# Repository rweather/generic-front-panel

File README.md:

Generic Front Panel
===================

This repository contains schematics and other information for a generic
front panel for 8-bit homebrew computers.

Here it is connected to my version of
[Ben Eater's 6502 Breadboard Computer](https://eater.net/6502),
running the "hello.s" example from the "src/6502" directory.
It is shown here after I typed ABCDEF on the keypad:

Here is a close-up of the front panel with a 3D-printed plate over the top:

The "print" directory contains an OpenSCAD file for the 3D-printable plate.
My brother, who is into 3D-printing, has a textured print bed for his printer.
He printed the plate upside down and the texturing gave the plate a nice finish.

## Features

The generic front panel has the following features:

* 6-digit seven segment display.
* 16-digit hexadecimal keypad.
* 3 extra keys for "CMD1", "CMD2", and "CMD3" which can be assigned
  any commands you like by your software.
* 1 extra key for a system reset button.
* 20-pin connector to the rest of your homebrew system.
* Power LED for the 5V power rail.

Note that this front panel requires software support.  It doesn't directly
operate the address bus, data bus, clock, and other control lines like
front panels of old.

What this front panel does do is make it easy to write a memory monitor in
software that can examine memory, modify memory, single-step, and so on.
The 6 displays can display a 16-bit address and an 8-bit byte.  Or anything
else you like, even words.

The seven segment displays, keypad buttons, and power LED are mounted
on the front side of the PCB.  All other components are mounted on the
back side.  The inline current limiting resistors are specified as 8-way
resistor arrays.  However, you could fit 8 regular resistors side by side
instead.

The front panel draws about 250mA from the 5V rail when all 48 segments
in the 7-segment displays and the power LED are lit.  About 5mA per segment.

I have provided drivers and examples for various CPU's under the
"src" directory.  Patches welcome for other CPU's and homebrew boards.

## Schematic and gerber files

* [PDF of the schematic](schematics/Generic_Front_Panel/PDF/Generic_Front_Panel.pdf)
* [Gerber files for manufacture](schematics/Generic_Front_Panel/Gerbers)

The dimensions of the PCB are 195mm x 90mm.  Five 3mm mounting holes are
provided for mounting behind a face plate: four corners and one in the
centre for added strength.

## Parts list

* 1 x Generic Front Panel FP-01 PCB
* 1 x 74HC138 3-line to 8-line decoder (74LS138 or 74HCT138 can be substituted)
* 1 x 74HC244 octal buffer / line driver (74LS244 or 74HCT244 can be substituted)
* 6 x 74HC259 addressable latch (74LS259 or 74HCT239 can be substituted)
* 6 x 100nF ceramic or monolithic capacitor
* 5 x 100pF ceramic capacitor
* 1 x 100uF electrolytic capacitor, rated for 6.3V or better
* 6 x 470 ohm DIP-16 resistor array
* 5 x 4.7K ohm resistor
* 1 x 220 ohm resistor (series resistor for 5mm power LED, adjust value for the LED's current rating)
* 1 x 5mm LED for the power LED (color is up to you)
* 6 x MAN71A 7-segment LED display (TIL-312 or Broadcom 5082-7611 can be substituted)
* 5 x 1N4148 diode
* 20 x 12mm push button plus keycaps
* 1 x 20-pin 2.54mm pitch terminal header or socket for the J1 connector

I recommend using DIP-14 sockets for the 7-segment LED displays to
raise the height of the displays up to roughly level with the top of the
push buttons plus keycaps.  Sockets for the other IC's are up to you;
I didn't bother.

Labels can be applied to the keycaps using a label maker and clear labels.

This is what the front and back of the PCB looks like once assembled
(I had only done a very basic board clean at this point so it is still a
little smudgy):

## 20-pin connector

The connector on the bottom of the PCB has the following pins:

<table border="1">
<tr><td><b>Pin</b></td><td><b>Description</b></td></tr>
<tr><td>1</td><td>+5V</td></tr>
<tr><td>2</td><td>D0</td></tr>
<tr><td>3</td><td>D1</td></tr>
<tr><td>4</td><td>D2</td></tr>
<tr><td>5</td><td>D3</td></tr>
<tr><td>6</td><td>D4</td></tr>
<tr><td>7</td><td>D5</td></tr>
<tr><td>8</td><td>D6</td></tr>
<tr><td>9</td><td>D7</td></tr>
<tr><td>10</td><td>A0</td></tr>
<tr><td>11</td><td>A1</td></tr>
<tr><td>12</td><td>A2</td></tr>
<tr><td>13</td><td>A3</td></tr>
<tr><td>14</td><td>A4</td></tr>
<tr><td>15</td><td>A5</td></tr>
<tr><td>16</td><td>Select Display (active low)</td></tr>
<tr><td>17</td><td>Select Keypad (active low)</td></tr>
<tr><td>18</td><td>Reset (active low)</td></tr>
<tr><td>19</td><td>GND</td></tr>
<tr><td>20</td><td>GND</td></tr>
</table>

## Chip selects

To interface to your homebrew computer, you will need to provide address
decoding for the two "chip select" lines "Select Display" and "Select Keypad".

You can put the front panel anywhere in memory or I/O space that is
aligned on a 64-byte boundary.  Only the bottom 6 address bits are
provided to the front panel.  You need to decode the upper 10 bits
(of a 16-bit address) yourself by some means.

"Select Display" should be low when the top-most bits of the address
match the location in memory where you want to put the display,
and when the bus is in a write cycle.  The display occupies 64 bytes
of memory space.

"Select Keypad" should be low when the top-most bits of the address
match the location in memory where you want to put the keypad,
and when the bus is in a read cycle.  The keypad occupies 32 bytes
of memory space.  It can overlap with the display in memory if that
is easier.

## Writing to the display

Each segment of the display has its own memory address.  Each digit
occupies 8 bytes of memory space, for the segments A, B, C, D, E, F, G,
and decimal point.  The displays are at offsets 0, 8, 16, 24, 32,
and 40 in the memory space.

Write a byte with the low bit set to 0 to a segment's address to turn
the segment on, or write a byte with the low bit set to 1 to turn the
segment off.  The segment will stay lit until modified or the power is
turned off.  The display is not multiplexed so there is no need to
constantly refresh.

Writing any byte value to offset 56 will turn all segments on.
This can be useful for testing.  Normally you will want to turn
everything off at startup time.

The "one byte per segment" design was borrowed from the Heathkit ET-3400.
74HC259 addressable latches are used to individually address each segment,
and to remember the state of the segment between writes.

## Reading from the keypad

The keypad consists of 5 rows of 4 keys.  The rows are associated with
address bits A0 to A4.  Scan through the keypad one row at a time,
setting one address bit to 0 and the rest to 1.  When you read from that
address, the bits that are set to zero indicate which keys are pressed
on that row.

<table border="1">
<tr><td><b>Address</b></td><td><b>Bit</b></td><td><b>Key</b></td></tr>
<tr><td>$XX1E (A0)</td><td>0</td><td>0</td></tr>
<tr><td>$XX1E (A0)</td><td>1</td><td>1</td></tr>
<tr><td>$XX1E (A0)</td><td>2</td><td>2</td></tr>
<tr><td>$XX1E (A0)</td><td>3</td><td>3</td></tr>
<tr><td>$XX1D (A1)</td><td>0</td><td>4</td></tr>
<tr><td>$XX1D (A1)</td><td>1</td><td>5</td></tr>
<tr><td>$XX1D (A1)</td><td>2</td><td>6</td></tr>
<tr><td>$XX1D (A1)</td><td>3</td><td>7</td></tr>
<tr><td>$XX1B (A2)</td><td>0</td><td>8</td></tr>
<tr><td>$XX1B (A2)</td><td>1</td><td>9</td></tr>
<tr><td>$XX1B (A2)</td><td>2</td><td>A</td></tr>
<tr><td>$XX1B (A2)</td><td>3</td><td>B</td></tr>
<tr><td>$XX17 (A3)</td><td>0</td><td>C</td></tr>
<tr><td>$XX17 (A3)</td><td>1</td><td>D</td></tr>
<tr><td>$XX17 (A3)</td><td>2</td><td>E</td></tr>
<tr><td>$XX17 (A3)</td><td>3</td><td>F</td></tr>
<tr><td>$XX0F (A4)</td><td>0</td><td>CMD1</td></tr>
<tr><td>$XX0F (A4)</td><td>1</td><td>CMD2</td></tr>
<tr><td>$XX0F (A4)</td><td>2</td><td>CMD3</td></tr>
<tr><td>$XX0F (A4)</td><td>3</td><td>(not used)</td></tr>
</table>

The "Reset" key is special.  It will pull pin 18 on the connector
down to GND when pressed.  It is assumed that a pull-up resistor and
debouncing capacitor are present on your main computer board.
If you want to use "Reset" for something else (such as a "CMD4" key),
you can connect pin 18 to an I/O pin on your main computer board.

The "rows as addresses" design was borrowed from the VZ200 / Laser 200.
Only a single 74HC244 bus transceiver is required to read the keypad.
Everything else is pushbuttons, diodes, resistors, and capacitors.

There are jumpers on the back of the board that can be cut to wire
up additional keys if you need more than 20.  The extra keys will
be available as bits 4 through 7.  The bits are pulled high if the
jumpers are uncut.

## License

MIT License.

## Contact

For more information on this project, to report bugs, or to suggest
improvements, please contact the author Rhys Weatherley via
[email](mailto:rhys.weatherley@gmail.com).

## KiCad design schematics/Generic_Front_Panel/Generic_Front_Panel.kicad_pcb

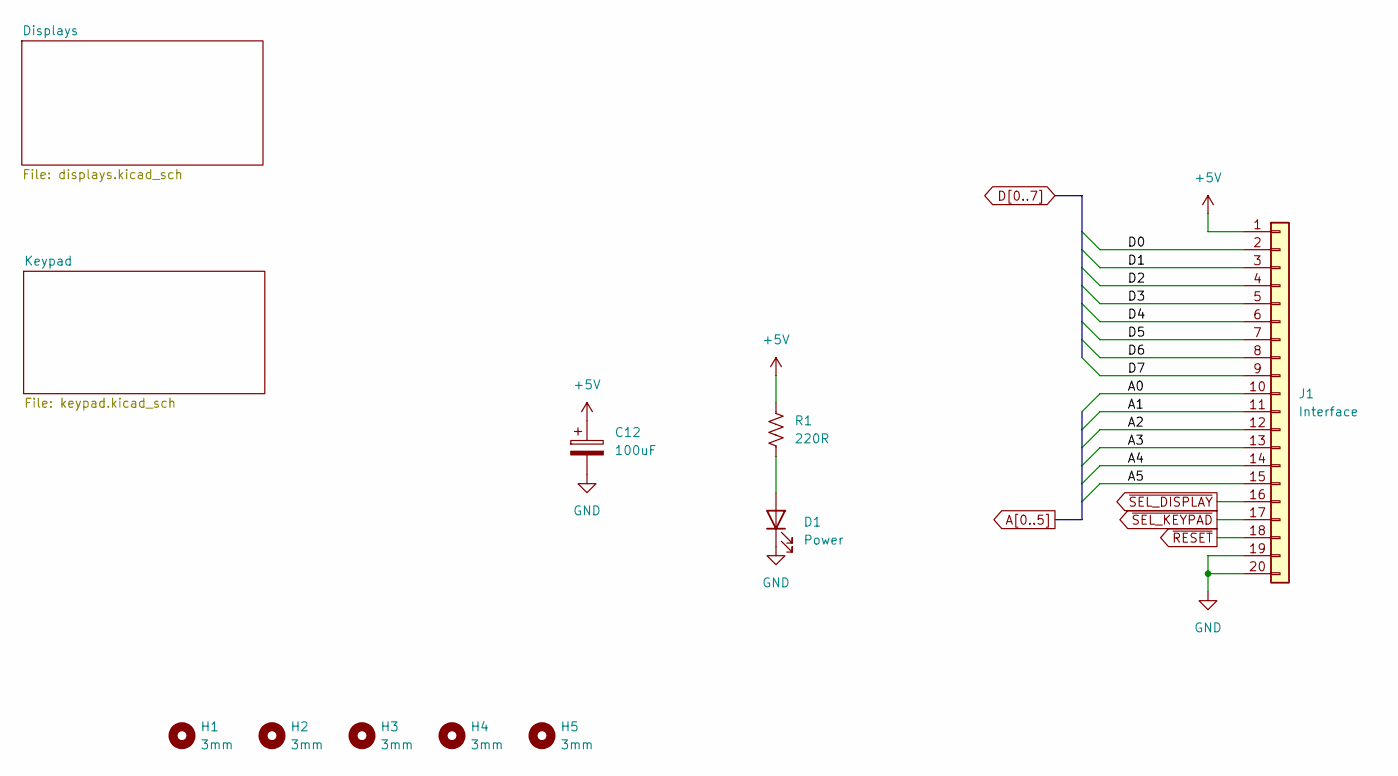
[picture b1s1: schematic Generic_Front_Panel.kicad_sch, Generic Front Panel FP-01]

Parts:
C12: 100uF; CP_Radial_D6.3mm_P2.50mm
D1: Power; LED_D5.0mm
H1, H2, H3, H4, H5: 3mm; MountingHole_3mm
J1: Interface; PinSocket_1x20_P2.54mm_Vertical
R1: 220R; R_Axial_DIN0207_L6.3mm_D2.5mm_P10.16mm_Horizontal

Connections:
+5V: C12.1, J1.1, R1.1; also elsewhere on the board
A0: J1.10; also elsewhere on the board
A1: J1.11; also elsewhere on the board
A2: J1.12; also elsewhere on the board
A3: J1.13; also elsewhere on the board
A4: J1.14; also elsewhere on the board
A5: J1.15; also elsewhere on the board
D0: J1.2; also elsewhere on the board
D1: J1.3; also elsewhere on the board
D2: J1.4; also elsewhere on the board
D3: J1.5; also elsewhere on the board
D4: J1.6; also elsewhere on the board
D5: J1.7; also elsewhere on the board
D6: J1.8; also elsewhere on the board
D7: J1.9; also elsewhere on the board
GND: C12.2, D1.1 (K), J1.19, J1.20; also elsewhere on the board
unnamed: D1.2 (A), R1.2
~RESET: J1.18; also elsewhere on the board
~SEL_DISPLAY: J1.16; also elsewhere on the board
~SEL_KEYPAD: J1.17; also elsewhere on the board

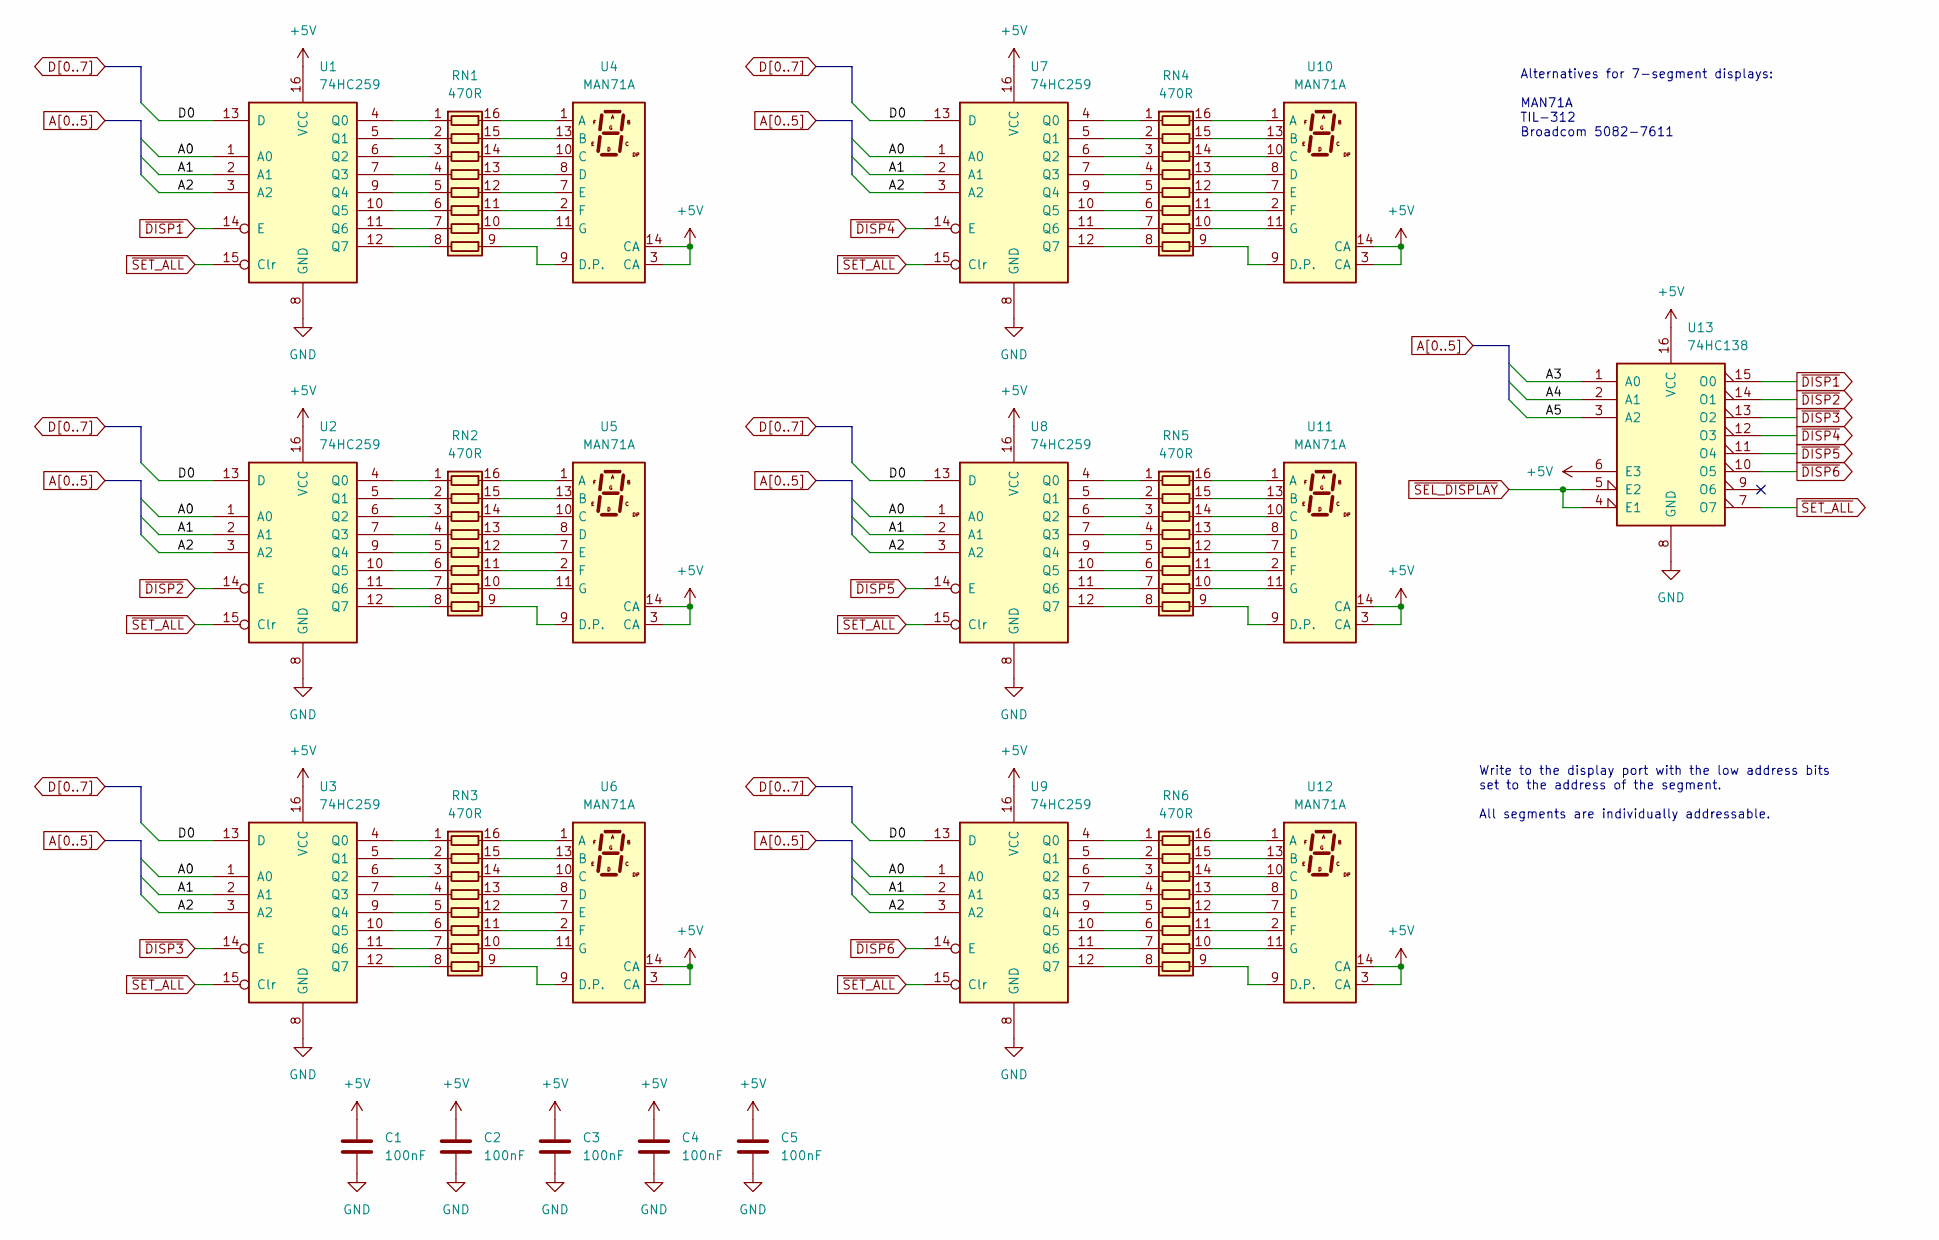
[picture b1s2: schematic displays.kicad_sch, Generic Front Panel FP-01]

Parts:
C1, C2, C3, C4, C5: 100nF; C_Disc_D6.0mm_W2.5mm_P5.00mm
RN1, RN2, RN3, RN4, RN5, RN6: 470R; DIP-16_W7.62mm
U1, U2, U3, U7, U8, U9: 74HC259; DIP-16_W7.62mm
U4, U5, U6, U10, U11, U12: MAN71A
U13: 74HC138; DIP-16_W7.62mm

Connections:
+5V: C1.1, C2.1, C3.1, C4.1, C5.1, U1.16 (VCC), U2.16 (VCC), U3.16 (VCC), U4.3 (CA), U4.14 (CA), U5.3 (CA), U5.14 (CA), U6.3 (CA), U6.14 (CA), U7.16 (VCC), U8.16 (VCC), U9.16 (VCC), U10.3 (CA), U10.14 (CA), U11.3 (CA), U11.14 (CA), U12.3 (CA), U12.14 (CA), U13.6 (E3), U13.16 (VCC); also elsewhere on the board
A0: U1.1 (A0), U2.1 (A0), U3.1 (A0), U7.1 (A0), U8.1 (A0), U9.1 (A0); also elsewhere on the board
A1: U1.2 (A1), U2.2 (A1), U3.2 (A1), U7.2 (A1), U8.2 (A1), U9.2 (A1); also elsewhere on the board
A2: U1.3 (A2), U2.3 (A2), U3.3 (A2), U7.3 (A2), U8.3 (A2), U9.3 (A2); also elsewhere on the board
A3: U13.1 (A0); also elsewhere on the board
A4: U13.2 (A1); also elsewhere on the board
A5: U13.3 (A2); also elsewhere on the board
D0: U1.13 (D), U2.13 (D), U3.13 (D), U7.13 (D), U8.13 (D), U9.13 (D); also elsewhere on the board
GND: C1.2, C2.2, C3.2, C4.2, C5.2, U1.8 (GND), U2.8 (GND), U3.8 (GND), U7.8 (GND), U8.8 (GND), U9.8 (GND), U13.8 (GND); also elsewhere on the board
unnamed: RN1.1 (R1.1), U1.4 (Q0)
unnamed: RN1.16 (R1.2), U4.1 (A)
unnamed: RN1.2 (R2.1), U1.5 (Q1)
unnamed: RN1.15 (R2.2), U4.13 (B)
unnamed: RN1.3 (R3.1), U1.6 (Q2)
unnamed: RN1.14 (R3.2), U4.10 (C)
unnamed: RN1.4 (R4.1), U1.7 (Q3)
unnamed: RN1.13 (R4.2), U4.8 (D)
unnamed: RN1.5 (R5.1), U1.9 (Q4)
unnamed: RN1.12 (R5.2), U4.7 (E)
unnamed: RN1.6 (R6.1), U1.10 (Q5)
unnamed: RN1.11 (R6.2), U4.2 (F)
unnamed: RN1.7 (R7.1), U1.11 (Q6)
unnamed: RN1.10 (R7.2), U4.11 (G)
unnamed: RN1.8 (R8.1), U1.12 (Q7)
unnamed: RN1.9 (R8.2), U4.9 (D.P.)
unnamed: RN2.1 (R1.1), U2.4 (Q0)
unnamed: RN2.16 (R1.2), U5.1 (A)
unnamed: RN2.2 (R2.1), U2.5 (Q1)
unnamed: RN2.15 (R2.2), U5.13 (B)
unnamed: RN2.3 (R3.1), U2.6 (Q2)
unnamed: RN2.14 (R3.2), U5.10 (C)
unnamed: RN2.4 (R4.1), U2.7 (Q3)
unnamed: RN2.13 (R4.2), U5.8 (D)
unnamed: RN2.5 (R5.1), U2.9 (Q4)
unnamed: RN2.12 (R5.2), U5.7 (E)
unnamed: RN2.6 (R6.1), U2.10 (Q5)
unnamed: RN2.11 (R6.2), U5.2 (F)
unnamed: RN2.7 (R7.1), U2.11 (Q6)
unnamed: RN2.10 (R7.2), U5.11 (G)
unnamed: RN2.8 (R8.1), U2.12 (Q7)
unnamed: RN2.9 (R8.2), U5.9 (D.P.)
unnamed: RN3.1 (R1.1), U3.4 (Q0)
unnamed: RN3.16 (R1.2), U6.1 (A)
unnamed: RN3.2 (R2.1), U3.5 (Q1)
unnamed: RN3.15 (R2.2), U6.13 (B)
unnamed: RN3.3 (R3.1), U3.6 (Q2)
unnamed: RN3.14 (R3.2), U6.10 (C)
unnamed: RN3.4 (R4.1), U3.7 (Q3)
unnamed: RN3.13 (R4.2), U6.8 (D)
unnamed: RN3.5 (R5.1), U3.9 (Q4)
unnamed: RN3.12 (R5.2), U6.7 (E)
unnamed: RN3.6 (R6.1), U3.10 (Q5)
unnamed: RN3.11 (R6.2), U6.2 (F)
unnamed: RN3.7 (R7.1), U3.11 (Q6)
unnamed: RN3.10 (R7.2), U6.11 (G)
unnamed: RN3.8 (R8.1), U3.12 (Q7)
unnamed: RN3.9 (R8.2), U6.9 (D.P.)
unnamed: RN4.1 (R1.1), U7.4 (Q0)
unnamed: RN4.16 (R1.2), U10.1 (A)
unnamed: RN4.2 (R2.1), U7.5 (Q1)
unnamed: RN4.15 (R2.2), U10.13 (B)
unnamed: RN4.3 (R3.1), U7.6 (Q2)
unnamed: RN4.14 (R3.2), U10.10 (C)
unnamed: RN4.4 (R4.1), U7.7 (Q3)
unnamed: RN4.13 (R4.2), U10.8 (D)
unnamed: RN4.5 (R5.1), U7.9 (Q4)
unnamed: RN4.12 (R5.2), U10.7 (E)
unnamed: RN4.6 (R6.1), U7.10 (Q5)
unnamed: RN4.11 (R6.2), U10.2 (F)
unnamed: RN4.7 (R7.1), U7.11 (Q6)
unnamed: RN4.10 (R7.2), U10.11 (G)
unnamed: RN4.8 (R8.1), U7.12 (Q7)
unnamed: RN4.9 (R8.2), U10.9 (D.P.)
unnamed: RN5.1 (R1.1), U8.4 (Q0)
unnamed: RN5.16 (R1.2), U11.1 (A)
unnamed: RN5.2 (R2.1), U8.5 (Q1)
unnamed: RN5.15 (R2.2), U11.13 (B)
unnamed: RN5.3 (R3.1), U8.6 (Q2)
unnamed: RN5.14 (R3.2), U11.10 (C)
unnamed: RN5.4 (R4.1), U8.7 (Q3)
unnamed: RN5.13 (R4.2), U11.8 (D)
unnamed: RN5.5 (R5.1), U8.9 (Q4)
unnamed: RN5.12 (R5.2), U11.7 (E)
unnamed: RN5.6 (R6.1), U8.10 (Q5)
unnamed: RN5.11 (R6.2), U11.2 (F)
unnamed: RN5.7 (R7.1), U8.11 (Q6)
unnamed: RN5.10 (R7.2), U11.11 (G)
unnamed: RN5.8 (R8.1), U8.12 (Q7)
unnamed: RN5.9 (R8.2), U11.9 (D.P.)
unnamed: RN6.1 (R1.1), U9.4 (Q0)
unnamed: RN6.16 (R1.2), U12.1 (A)
unnamed: RN6.2 (R2.1), U9.5 (Q1)
unnamed: RN6.15 (R2.2), U12.13 (B)
unnamed: RN6.3 (R3.1), U9.6 (Q2)
unnamed: RN6.14 (R3.2), U12.10 (C)
unnamed: RN6.4 (R4.1), U9.7 (Q3)
unnamed: RN6.13 (R4.2), U12.8 (D)
unnamed: RN6.5 (R5.1), U9.9 (Q4)
unnamed: RN6.12 (R5.2), U12.7 (E)
unnamed: RN6.6 (R6.1), U9.10 (Q5)
unnamed: RN6.11 (R6.2), U12.2 (F)
unnamed: RN6.7 (R7.1), U9.11 (Q6)
unnamed: RN6.10 (R7.2), U12.11 (G)
unnamed: RN6.8 (R8.1), U9.12 (Q7)
unnamed: RN6.9 (R8.2), U12.9 (D.P.)
~DISP1: U1.14 (E), U13.15 (O0)
~DISP2: U2.14 (E), U13.14 (O1)
~DISP3: U3.14 (E), U13.13 (O2)
~DISP4: U7.14 (E), U13.12 (O3)
~DISP5: U8.14 (E), U13.11 (O4)
~DISP6: U9.14 (E), U13.10 (O5)
~SEL_DISPLAY: U13.4 (E1), U13.5 (E2); also elsewhere on the board
~SET_ALL: U1.15 (Clr), U2.15 (Clr), U3.15 (Clr), U7.15 (Clr), U8.15 (Clr), U9.15 (Clr), U13.7 (O7)

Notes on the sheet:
Write to the display port with the low address bits set to the address of the segment. All segments are individually addressable.
Alternatives for 7-segment displays: MAN71A TIL-312 Broadcom 5082-7611

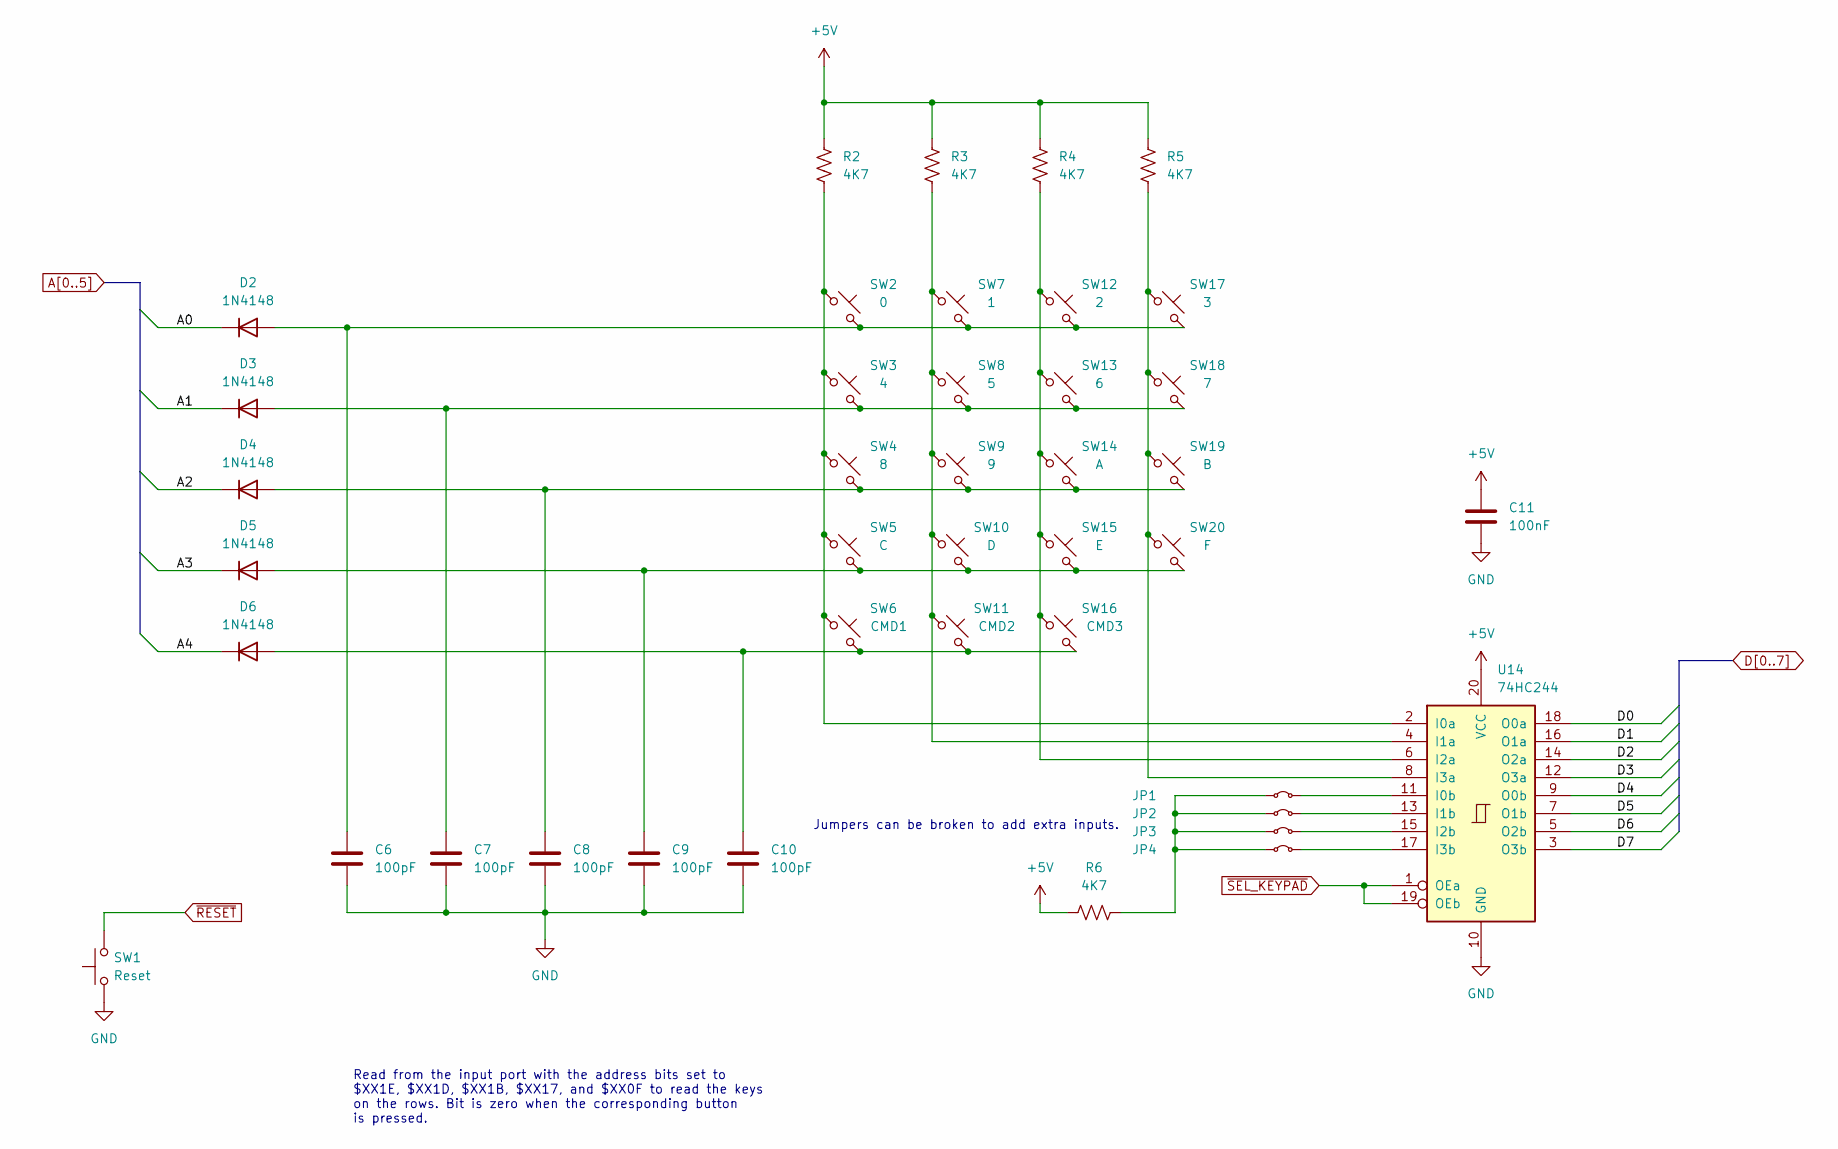
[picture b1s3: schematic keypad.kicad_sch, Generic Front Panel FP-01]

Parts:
C6, C7, C8, C9, C10: 100pF; C_Disc_D6.0mm_W2.5mm_P5.00mm
C11: 100nF; C_Disc_D6.0mm_W2.5mm_P5.00mm
D2, D3, D4, D5, D6: 1N4148; D_DO-35_SOD27_P7.62mm_Horizontal
JP1, JP2, JP3, JP4: SolderJumper-2_P1.3mm_Bridged_RoundedPad1.0x1.5mm
R2, R3, R4, R5, R6: 4K7; R_Axial_DIN0207_L6.3mm_D2.5mm_P10.16mm_Horizontal
SW1: Reset; SW_PUSH-12mm
SW2: 0; SW_PUSH-12mm
SW3: 4; SW_PUSH-12mm
SW4: 8; SW_PUSH-12mm
SW5: C; SW_PUSH-12mm
SW6: CMD1; SW_PUSH-12mm
SW7: 1; SW_PUSH-12mm
SW8: 5; SW_PUSH-12mm
SW9: 9; SW_PUSH-12mm
SW10: D; SW_PUSH-12mm
SW11: CMD2; SW_PUSH-12mm
SW12: 2; SW_PUSH-12mm
SW13: 6; SW_PUSH-12mm
SW14: A; SW_PUSH-12mm
SW15: E; SW_PUSH-12mm
SW16: CMD3; SW_PUSH-12mm
SW17: 3; SW_PUSH-12mm
SW18: 7; SW_PUSH-12mm
SW19: B; SW_PUSH-12mm
SW20: F; SW_PUSH-12mm
U14: 74HC244; DIP-20_W7.62mm

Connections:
+5V: C11.1, R2.1, R3.1, R4.1, R5.1, R6.1, U14.20 (VCC); also elsewhere on the board
A0: D2.1 (K); also elsewhere on the board
A1: D3.1 (K); also elsewhere on the board
A2: D4.1 (K); also elsewhere on the board
A3: D5.1 (K); also elsewhere on the board
A4: D6.1 (K); also elsewhere on the board
D0: U14.18 (O0a); also elsewhere on the board
D1: U14.16 (O1a); also elsewhere on the board
D2: U14.14 (O2a); also elsewhere on the board
D3: U14.12 (O3a); also elsewhere on the board
D4: U14.9 (O0b); also elsewhere on the board
D5: U14.7 (O1b); also elsewhere on the board
D6: U14.5 (O2b); also elsewhere on the board
D7: U14.3 (O3b); also elsewhere on the board
GND: C6.2, C7.2, C8.2, C9.2, C10.2, C11.2, SW1.1, U14.10 (GND); also elsewhere on the board
unnamed: C6.1, D2.2 (A), SW2.2, SW7.2, SW12.2, SW17.2
unnamed: C7.1, D3.2 (A), SW3.2, SW8.2, SW13.2, SW18.2
unnamed: C8.1, D4.2 (A), SW4.2, SW9.2, SW14.2, SW19.2
unnamed: C9.1, D5.2 (A), SW5.2, SW10.2, SW15.2, SW20.2
unnamed: C10.1, D6.2 (A), SW6.2, SW11.2, SW16.2
unnamed: JP1.1 (A), JP2.1 (A), JP3.1 (A), JP4.1 (A), R6.2
unnamed: JP1.2 (B), U14.11 (I0b)
unnamed: JP2.2 (B), U14.13 (I1b)
unnamed: JP3.2 (B), U14.15 (I2b)
unnamed: JP4.2 (B), U14.17 (I3b)
unnamed: R2.2, SW2.1, SW3.1, SW4.1, SW5.1, SW6.1, U14.2 (I0a)
unnamed: R3.2, SW7.1, SW8.1, SW9.1, SW10.1, SW11.1, U14.4 (I1a)
unnamed: R4.2, SW12.1, SW13.1, SW14.1, SW15.1, SW16.1, U14.6 (I2a)
unnamed: R5.2, SW17.1, SW18.1, SW19.1, SW20.1, U14.8 (I3a)
~RESET: SW1.2; also elsewhere on the board
~SEL_KEYPAD: U14.1 (OEa), U14.19 (OEb); also elsewhere on the board

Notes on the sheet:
Read from the input port with the address bits set to $XX1E, $XX1D, $XX1B, $XX17, and $XX0F to read the keys on the rows. Bit is zero when the corresponding button is pressed.
Jumpers can be broken to add extra inputs.

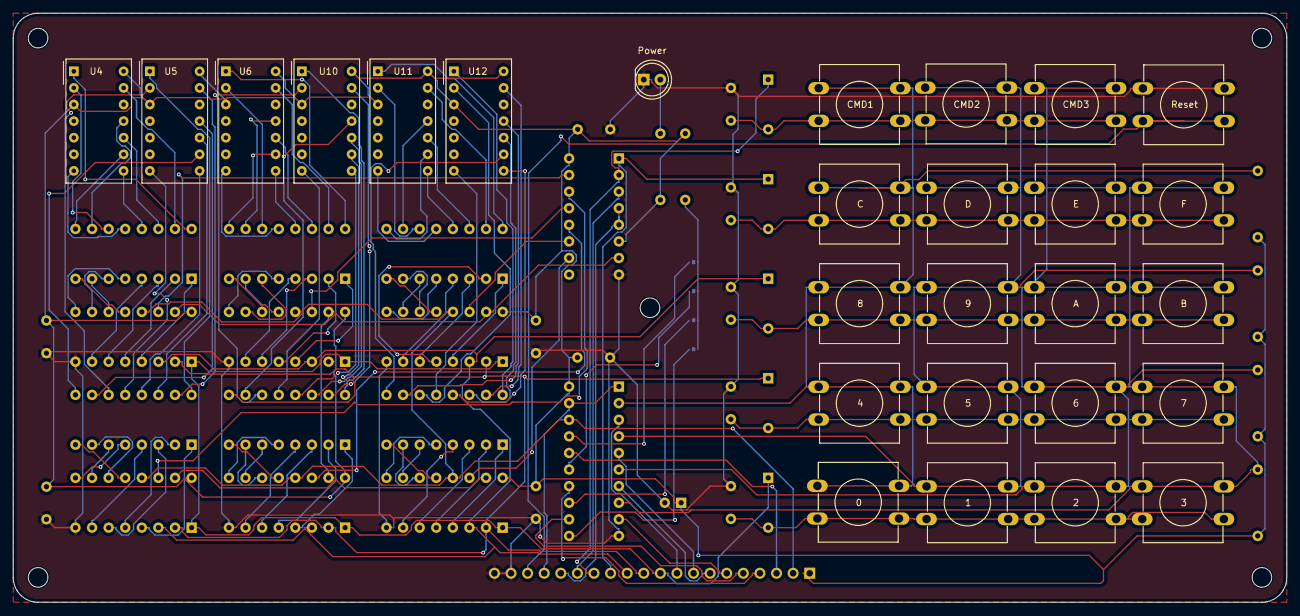
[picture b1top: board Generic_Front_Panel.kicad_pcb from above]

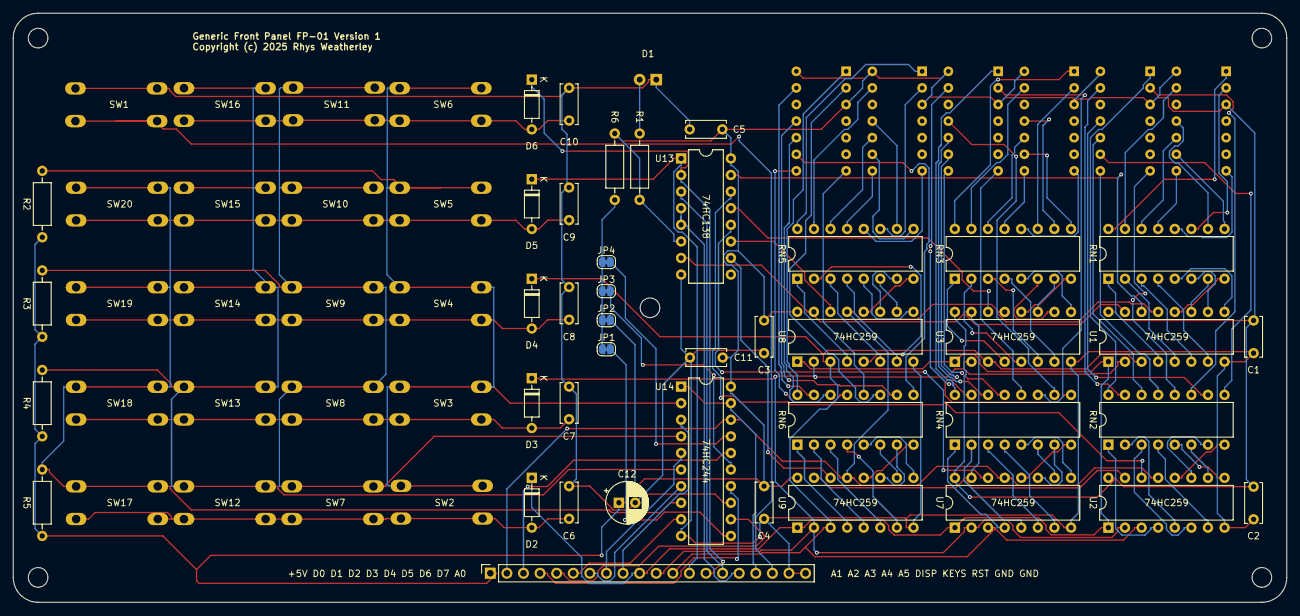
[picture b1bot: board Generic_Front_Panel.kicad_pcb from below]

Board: 2 copper layers, 194.9 x 90.2 mm, 74 parts (42 on the bottom side), 137 nets.

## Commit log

2025-05-10 Schematics and PCB layout for the generic front panel
2025-05-11 Add README and LICENSE
2025-05-11 Front panel driver for 6502-based computers
2025-05-13 Front panel driver for 1802-based computers
2025-05-14 Pre-invert the 7-segment bit patterns
2025-05-14 Make the 1802 driver more position-independent for I/O mapping
2025-05-16 Update filter capacitor to 100uF
2025-05-16 Document the maximum current draw of the panel
2025-05-17 Fixes to the hello examples
2025-05-17 Debouncing key presses in the 6502 version of the driver
2025-05-17 Add a picture of the 6502 + front panel working
2025-05-18 Add more README material and pictures of the front and back of the PCB
2025-05-24 Machine monitor for 6502
2025-05-25 Single-stepping support for the 6502 monitor
2025-05-25 OpenSCAD file for a 3D-printable front plate for the panel
2025-05-25 Simplify the driver code
2025-05-25 Improvements to single-stepping mode
2025-05-28 Picture of the 3D-printed front plate
2025-05-31 Get the 1802 version of the front panel driver to work

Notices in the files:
schematics/Generic_Front_Panel/Generic_Front_Panel.kicad_pcb:
Copyright (c) 2025 Rhys Weatherley
